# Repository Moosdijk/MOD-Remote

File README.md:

# MOD-Remote
This repository contains the source code and design files for the MOD Remote, a device which came out of my final thesis at Industrial Design at the Technical University in Eindhoven.

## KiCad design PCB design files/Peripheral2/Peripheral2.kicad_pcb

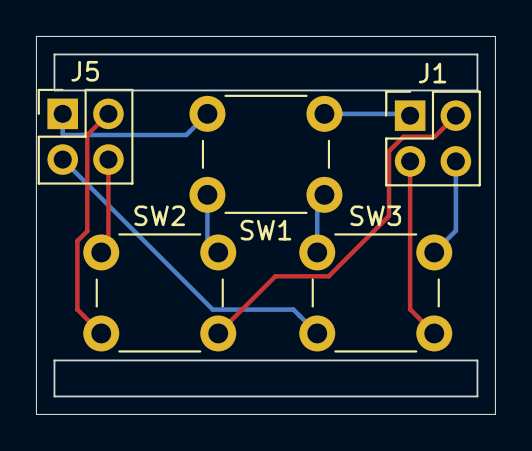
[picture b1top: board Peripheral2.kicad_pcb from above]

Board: 2 copper layers, 25.5 x 21.0 mm, 5 parts (0 on the bottom side), 4 nets.

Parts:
J1, J5: Conn_01x04_Female; PinHeader_2x02_P2.54mm_Vertical
SW1, SW2, SW3: SW_Push; SW_PUSH_6mm_H5mm

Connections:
unnamed: J1.1, J5.1, SW1.2
unnamed: J1.2, J5.2, SW2.2
unnamed: J1.3, J5.3, SW3.2
unnamed: J1.4, J5.4, SW1.1, SW2.1, SW3.1

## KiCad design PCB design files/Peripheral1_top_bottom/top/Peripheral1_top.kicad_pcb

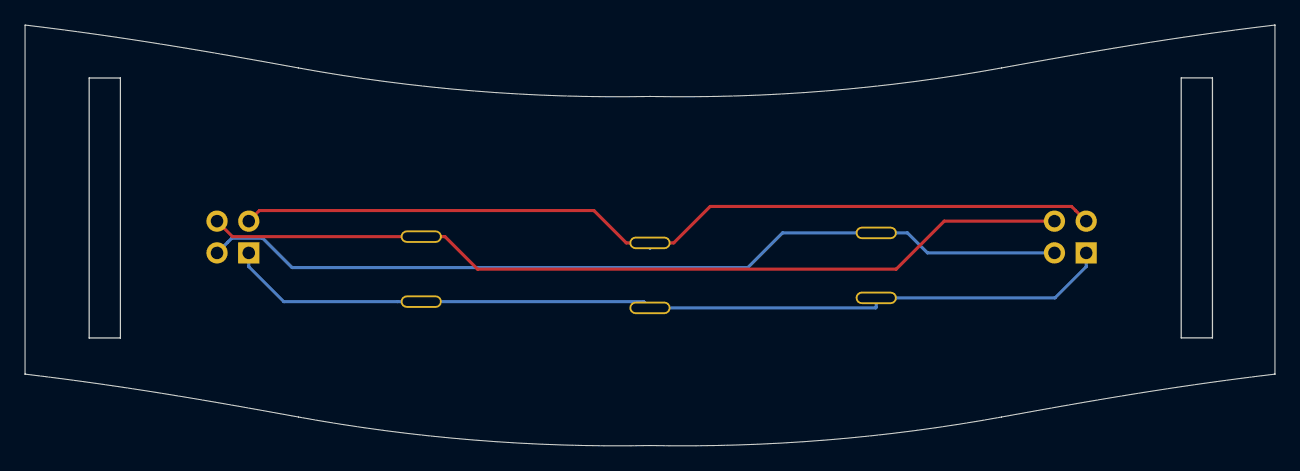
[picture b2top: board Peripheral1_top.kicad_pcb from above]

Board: 2 copper layers, 100.0 x 33.7 mm, 5 parts (0 on the bottom side), 4 nets.

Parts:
J5, J6: Conn_01x04_Female; PinHeader_2x02_P2.54mm_Vertical
SW3, SW6, SW7: SW_Push; reset_button_2.8mm

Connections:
unnamed: J5.1, J6.1, SW3.1, SW6.1, SW7.1
unnamed: J5.2, J6.2, SW3.2
unnamed: J5.3, J6.3, SW6.2
unnamed: J5.4, J6.4, SW7.2

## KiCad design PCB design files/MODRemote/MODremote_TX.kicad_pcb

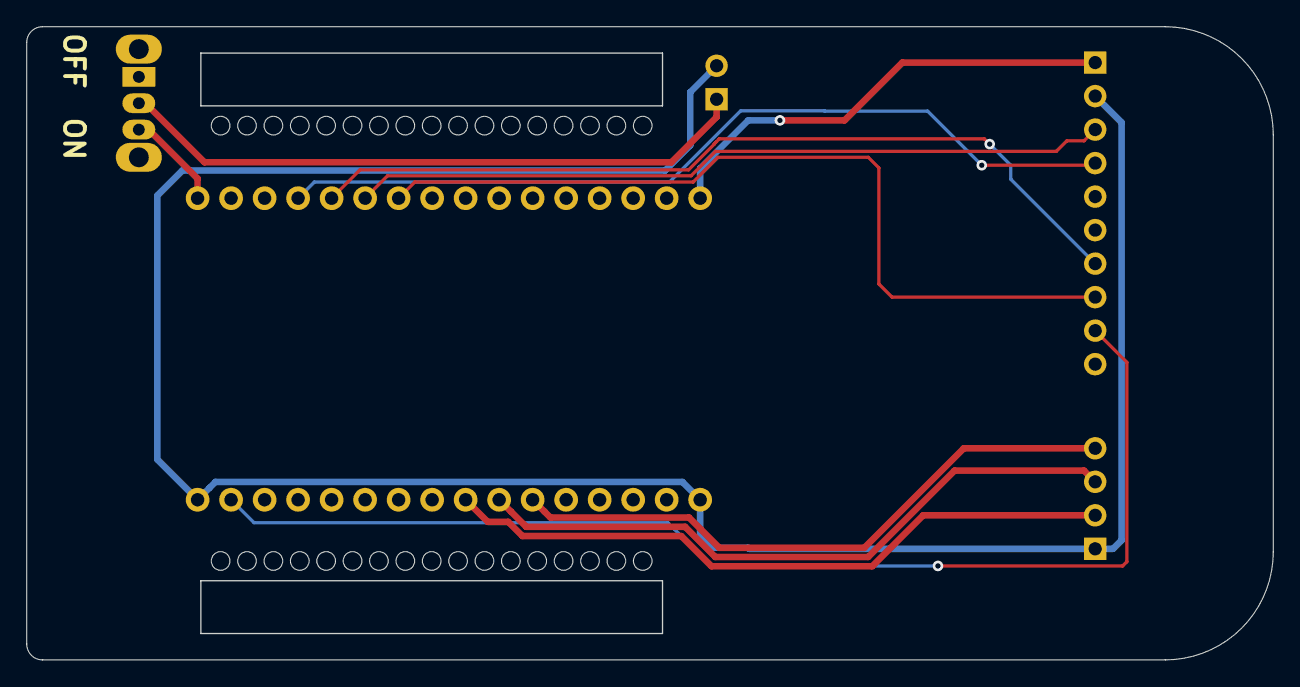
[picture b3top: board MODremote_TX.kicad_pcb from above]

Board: 2 copper layers, 94.5 x 48.0 mm, 5 parts (0 on the bottom side), 12 nets.

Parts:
J1: To MPU9250; PinHeader_1x10_P2.54mm_Vertical
J2: Conn_01x04_Male; PinHeader_1x04_P2.54mm_Vertical
J3: Conn_01x02; PinHeader_1x02_P2.54mm_Vertical
SW1: SW_Push_SPDT; SW_CuK_OS102011MA1QN1_SPDT_Angled
U1: LolinD32

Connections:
+3V3: J1.1, U1.1
+BATT: SW1.3, U1.16
GND: J1.2, J2.1, J3.2, U1.17, U1.32
unnamed: J1.3, U1.11
unnamed: J1.4, U1.13
unnamed: J1.7, U1.12
unnamed: J1.8, U1.10
unnamed: J1.9, U1.18
unnamed: J2.2, U1.25
unnamed: J2.3, U1.26
unnamed: J2.4, U1.27
unnamed: J3.1, SW1.2
